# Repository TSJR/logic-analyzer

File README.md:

# TTL Logic Analyzer

Breadboard and PCB-based logic analyzer built from discrete 74xx TTL logic, SRAM, and multiplexed LED matrix displays.

## Overview
This project aims to build a fully discrete logic analyzer without using a microcontroller. The analyzer captures digital bus states into SRAM and displays captured samples on multiplexed LED matrices.

Project is currently in a state of active prototyping.

*This repository also contains a [closely related project](attiny-logic-analyzer) using an MCU-based design with 24 channels. 

## Features
- Fully TTL-based architecture
- SRAM-based sample capture
- Multiplexed LED matrix display
- External/internal clock modes
- Planned trigger and halt functionality
- Modular PCB-based design

## Current Status
Current prototype supports:
- 64ish x 8 sample memory subsystem
- LED matrix display driver
- Breadboard proof-of-concept testing

Known issues:
- Breadboard noise/signal integrity
- Clock edge instability
- Limited memory

## Architecture
Main subsystems:
- Capture memory subsystem
- Address/control logic
- Clock generation and edge conditioning
- Display subsystem

## Relevant Simulation Subcircuits
- `analyzer_7400.circ` — 74xx IC Implementation     
    - **mem_64x8**: Full memory subsystem test built from 74xx-style chips using four `ram_unit` subcircuits.
    - **ram_unit**: 16x8 RAM unit built from 74xx-style chips; used as the building block for `mem_64x8`.
    - **disp_16x16**: Limited-capacity display subsystem test; does not yet include the physical driver circuitry needed for hardware.
- `analyzer_ttl.circ` — Abstract Logic Implementation
    - **mem_64x8_async**: Asynchronous version of the 64x8 memory subsystem; same capacity as the final intended design.
    - **disp_16x32**: Full-capacity display subsystem test.

More detailed documentation:
- [Analyzer Architecture](docs/architecture.md)
- [Build Log](docs/build-log.md)
- [Simulation Subcircuits](simulations/sim-subcircuits.md)

## Repository Structure
```text
docs/                   Docs and architecture notes
images/                 Build photos and diagrams
pcb/                    KiCad PCB projects
simulations/            Logisim simulations
attiny-logic-analyzer/   Related MCU-based project
```

## Hardware
Main IC families/components:
- 74xx logic family chips
- ULN2803 and UDN2981

## Future Plans
- Expand memory depth
- Modular memory pcb
- Trigger logic
- Improved clock conditioning
- PCB-based final implementation

If the project expands beyond basic TTL hardware, plans may include
- USB interface
- OLED display
- Many more channels
- Higher sampling rate 

## License
MIT License

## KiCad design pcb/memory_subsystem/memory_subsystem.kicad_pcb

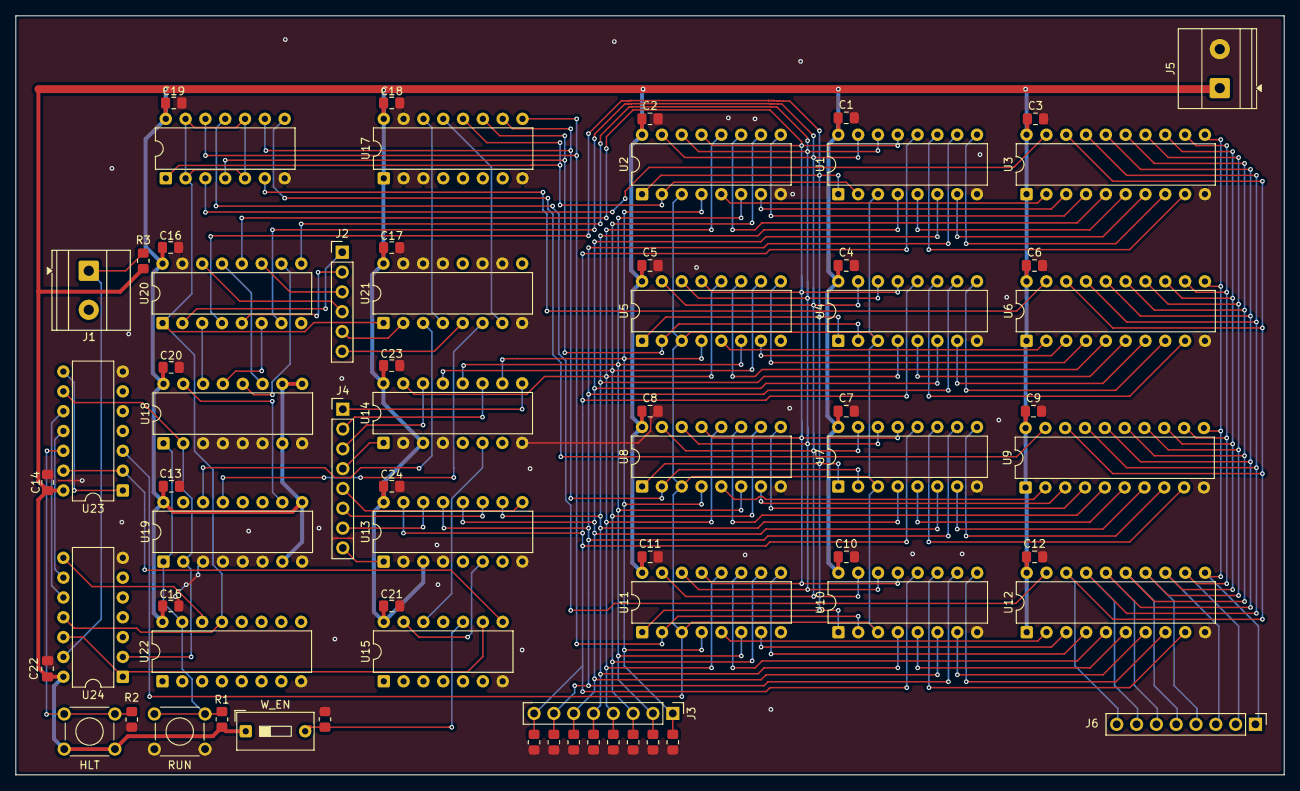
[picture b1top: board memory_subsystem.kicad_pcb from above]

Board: 2 copper layers, 162.6 x 97.3 mm, 69 parts (0 on the bottom side), 100 nets.

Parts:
C1, C2, C3, C4, C5, C6, C7, C8, C9, C10, C11, C12, C13, C14, C15, C16, C17, C18, C19, C20, C21, C22, C23, C24: C; C_0805_2012Metric_Pad1.18x1.45mm_HandSolder
HLT: HLT; SW_TH_Tactile_Omron_B3F-100x
J1: CLK; TerminalBlock_Phoenix_MKDS-1,5-2_1x02_P5.00mm_Horizontal
J2: Addr In; PinHeader_1x06_P2.54mm_Vertical
J3: Data In; PinHeader_1x08_P2.54mm_Vertical
J4: Word In; PinHeader_1x08_P2.54mm_Vertical
J5: Power; TerminalBlock_Phoenix_MKDS-1,5-2_1x02_P5.00mm_Horizontal
J6: Data Out; PinHeader_1x08_P2.54mm_Vertical
R1, R2, R3, R4, R5, R6, R7, R8, R9, R10, R11, R12: R; R_0805_2012Metric_Pad1.20x1.40mm_HandSolder
RUN: RUN; SW_TH_Tactile_Omron_B3F-100x
U1, U2, U4, U5, U7, U8, U10, U11: DIP-16_W7.62mm
U3, U6, U9, U12: 74LS245; DIP-20_W7.62mm
U13, U14: 74LS85; DIP-16_W7.62mm
U15: 74LS21; DIP-14_W7.62mm
U16, U23: 74LS32; DIP-14_W7.62mm
U17: 74LS139; DIP-16_W7.62mm
U18, U19: 74LS161; DIP-16_W7.62mm
U20, U21: 74LS157; DIP-16_W7.62mm
U22: 74LS279; DIP-16_W7.62mm
U24: 74LS14; DIP-14_W7.62mm
W_EN: W_EN; SW_DIP_SPSTx01_Slide_9.78x4.72mm_W7.62mm_P2.54mm

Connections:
+5V: C1.1, C2.1, C3.1, C4.1, C5.1, C6.1, C7.1, C8.1, C9.1, C10.1, C11.1, C12.1, C13.2, C14.2, C15.2, C16.2, C17.1, C18.2, C19.2, C20.2, C21.2, C22.2, C23.2, C24.2, HLT.1, J5.1, R1.1, R3.2, U1.16 (VCC), U2.16 (VCC), U3.1 (A->B), U3.20 (VCC), U4.16 (VCC), U5.16 (VCC), U6.1 (A->B), U6.20 (VCC), U7.16 (VCC), U8.16 (VCC), U9.1 (A->B), U9.20 (VCC), U10.16 (VCC), U11.16 (VCC), U12.1 (A->B), U12.20 (VCC), U13.3 (Ia=b), U13.16 (VCC), U14.3 (Ia=b), U14.16 (VCC), U15.14 (VCC), U16.14 (VCC), U17.1 (E), U17.16 (VCC), U18.7 (CEP), U18.9 (~PE), U18.10 (CET), U18.16 (VCC), U19.7 (CEP), U19.9 (~PE), U19.16 (VCC), U20.16 (VCC), U21.16 (VCC), U22.16 (VCC), U23.14 (VCC), U24.14 (VCC), W_EN.1
/Address Selector/Addr0: J2.1, U20.2 (I0a)
/Address Selector/Addr1: J2.2, U20.5 (I0b)
/Address Selector/Addr2: J2.3, U20.11 (I0c)
/Address Selector/Addr3: J2.4, U20.14 (I0d)
/Address Selector/Addr4: J2.5, U21.2 (I0a)
/Address Selector/Addr5: J2.6, U21.5 (I0b)
/Address Selector/CS0: U1.2 (CS), U2.2 (CS), U16.1, U17.12 (O0)
/Address Selector/CS1: U4.2 (CS), U5.2 (CS), U16.4, U17.11 (O1)
/Address Selector/CS2: U7.2 (CS), U8.2 (CS), U16.9, U17.10 (O2)
/Address Selector/CS3: U10.2 (CS), U11.2 (CS), U16.12, U17.9 (O3)
/Address Selector/OE0: U3.19 (CE), U16.3
/Address Selector/OE1: U6.19 (CE), U16.6
/Address Selector/OE2: U9.19 (CE), U16.8
/Address Selector/OE3: U12.19 (CE), U16.11
/Address Selector/RUN: R1.2, RUN.2, U18.1 (~MR), U19.1 (~MR), U22.15 (~S)
/Address Selector/R/W: U16.2, U16.5, U16.10, U16.13, U20.1 (S), U21.1 (S), U22.13 (Q), U24.11
/Address Selector/SAddr0: U1.1 (A0), U2.1 (A0), U4.1 (A0), U5.1 (A0), U7.1 (A0), U8.1 (A0), U10.1 (A0), U11.1 (A0), U20.4 (Za)
/Address Selector/SAddr1: U1.15 (A1), U2.15 (A1), U4.15 (A1), U5.15 (A1), U7.15 (A1), U8.15 (A1), U10.15 (A1), U11.15 (A1), U20.7 (Zb)
/Address Selector/SAddr2: U1.14 (A2), U2.14 (A2), U4.14 (A2), U5.14 (A2), U7.14 (A2), U8.14 (A2), U10.14 (A2), U11.14 (A2), U20.9 (Zc)
/Address Selector/SAddr3: U1.13 (A3), U2.13 (A3), U4.13 (A3), U5.13 (A3), U7.13 (A3), U8.13 (A3), U10.13 (A3), U11.13 (A3), U20.12 (Zd)
/Address Selector/SAddr4: U17.14 (A0), U21.4 (Za)
/Address Selector/SAddr5: U17.13 (A1), U21.7 (Zb)
/Address Selector/counter_CLK: U18.2 (CP), U19.2 (CP), U23.9, U24.2
/Control Logic/CLK: J1.1 (Pin_1_1), R3.1, U24.13
/Control Logic/RAM_WE: U1.3 (WE), U2.3 (WE), U4.3 (WE), U5.3 (WE), U7.3 (WE), U8.3 (WE), U10.3 (WE), U11.3 (WE), U23.3
/Control Logic/man_HLT: HLT.2, R2.2, U23.12
/Control Logic/word_CLK: U15.9, U24.1, U24.12
/Control Logic/word_HLT: U15.8, U23.2, U23.13
/Din0: J3.1, R5.1, U2.4 (D0), U5.4 (D0), U8.4 (D0), U11.4 (D0), U14.10 (A0)
/Din1: J3.2, R6.1, U2.6 (D1), U5.6 (D1), U8.6 (D1), U11.6 (D1), U14.12 (A1)
/Din2: J3.3, R7.1, U2.10 (D2), U5.10 (D2), U8.10 (D2), U11.10 (D2), U14.13 (A2)
/Din3: J3.4, R8.1, U2.12 (D3), U5.12 (D3), U8.12 (D3), U11.12 (D3), U14.15 (A3)
/Din4: J3.5, R9.1, U1.4 (D0), U4.4 (D0), U7.4 (D0), U10.4 (D0), U13.10 (A0)
/Din5: J3.6, R10.1, U1.6 (D1), U4.6 (D1), U7.6 (D1), U10.6 (D1), U13.12 (A1)
/Din6: J3.7, R11.1, U1.10 (D2), U4.10 (D2), U7.10 (D2), U10.10 (D2), U13.13 (A2)
/Din7: J3.8, R12.1, U1.12 (D3), U4.12 (D3), U7.12 (D3), U10.12 (D3), U13.15 (A3)
/Out0: J6.8, U3.18 (B0), U6.18 (B0), U9.18 (B0), U12.18 (B0)
/Out1: J6.7, U3.17 (B1), U6.17 (B1), U9.17 (B1), U12.17 (B1)
/Out2: J6.6, U3.16 (B2), U6.16 (B2), U9.16 (B2), U12.16 (B2)
/Out3: J6.5, U3.15 (B3), U6.15 (B3), U9.15 (B3), U12.15 (B3)
/Out4: J6.4, U3.14 (B4), U6.14 (B4), U9.14 (B4), U12.14 (B4)
/Out5: J6.3, U3.13 (B5), U6.13 (B5), U9.13 (B5), U12.13 (B5)
/Out6: J6.2, U3.12 (B6), U6.12 (B6), U9.12 (B6), U12.12 (B6)
/Out7: J6.1, U3.11 (B7), U6.11 (B7), U9.11 (B7), U12.11 (B7)
/Win0: J4.1, U14.9 (B0)
/Win1: J4.2, U14.11 (B1)
/Win2: J4.3, U14.14 (B2)
/Win3: J4.4, U14.1 (B3)
/Win4: J4.5, U13.9 (B0)
/Win5: J4.6, U13.11 (B1)
/Win6: J4.7, U13.14 (B2)
/Win7: J4.8, U13.1 (B3)
/Word Comparator/word_EN: R4.1, U15.10, W_EN.2
GND: C1.2, C2.2, C3.2, C4.2, C5.2, C6.2, C7.2, C8.2, C9.2, C10.2, C11.2, C12.2, C13.1, C14.1, C15.1, C16.1, C17.2, C18.1, C19.1, C20.1, C21.1, C22.1, C23.1, C24.1, J5.2, R2.1, R4.2, R5.2, R6.2, R7.2, R8.2, R9.2, R10.2, R11.2, R12.2, RUN.1, U1.8 (GND), U2.8 (GND), U3.10 (GND), U4.8 (GND), U5.8 (GND), U6.10 (GND), U7.8 (GND), U8.8 (GND), U9.10 (GND), U10.8 (GND), U11.8 (GND), U12.10 (GND), U13.2 (Ia<b), U13.4 (Ia>b), U13.8 (GND), U14.2 (Ia<b), U14.4 (Ia>b), U14.8 (GND), U15.7 (GND), U16.7 (GND), U17.2 (A0), U17.3 (A1), U17.8 (GND), U17.15 (E), U18.3 (D0), U18.4 (D1), U18.5 (D2), U18.6 (D3), U18.8 (GND), U19.3 (D0), U19.4 (D1), U19.5 (D2), U19.6 (D3), U19.8 (GND), U20.8 (GND), U20.15 (E), U21.8 (GND), U21.10 (I1c), U21.11 (I0c), U21.13 (I1d), U21.14 (I0d), U21.15 (E), U22.8 (GND), U23.7 (GND), U24.7 (GND)
unnamed: U1.5 (O0), U3.6 (A4)
unnamed: U1.7 (O1), U3.7 (A5)
unnamed: U1.9 (O2), U3.8 (A6)
unnamed: U1.11 (O3), U3.9 (A7)
unnamed: U2.5 (O0), U3.2 (A0)
unnamed: U2.7 (O1), U3.3 (A1)
unnamed: U2.9 (O2), U3.4 (A2)
unnamed: U2.11 (O3), U3.5 (A3)
unnamed: U4.5 (O0), U6.6 (A4)
unnamed: U4.7 (O1), U6.7 (A5)
unnamed: U4.9 (O2), U6.8 (A6)
unnamed: U4.11 (O3), U6.9 (A7)
unnamed: U5.5 (O0), U6.2 (A0)
unnamed: U5.7 (O1), U6.3 (A1)
unnamed: U5.9 (O2), U6.4 (A2)
unnamed: U5.11 (O3), U6.5 (A3)
unnamed: U7.5 (O0), U9.6 (A4)
unnamed: U7.7 (O1), U9.7 (A5)
unnamed: U7.9 (O2), U9.8 (A6)
unnamed: U7.11 (O3), U9.9 (A7)
unnamed: U8.5 (O0), U9.2 (A0)
unnamed: U8.7 (O1), U9.3 (A1)
unnamed: U8.9 (O2), U9.4 (A2)
unnamed: U8.11 (O3), U9.5 (A3)
unnamed: U10.5 (O0), U12.6 (A4)
unnamed: U10.7 (O1), U12.7 (A5)
unnamed: U10.9 (O2), U12.8 (A6)
unnamed: U10.11 (O3), U12.9 (A7)
unnamed: U11.5 (O0), U12.2 (A0)
unnamed: U11.7 (O1), U12.3 (A1)
unnamed: U11.9 (O2), U12.4 (A2)
unnamed: U11.11 (O3), U12.5 (A3)
unnamed: U13.6 (Oa=b), U15.13
unnamed: U14.6 (Oa=b), U15.12
unnamed: U18.14 (Q0), U20.3 (I1a)
unnamed: U18.13 (Q1), U20.6 (I1b)
unnamed: U18.12 (Q2), U20.10 (I1c)
unnamed: U18.11 (Q3), U20.13 (I1d)
unnamed: U18.15 (TC), U19.10 (CET)
unnamed: U19.14 (Q0), U21.3 (I1a)
unnamed: U19.13 (Q1), U21.6 (I1b)
unnamed: U22.14 (~R), U24.8
unnamed: U23.1, U23.8
unnamed: U23.10, U24.10
unnamed: U23.11, U24.9

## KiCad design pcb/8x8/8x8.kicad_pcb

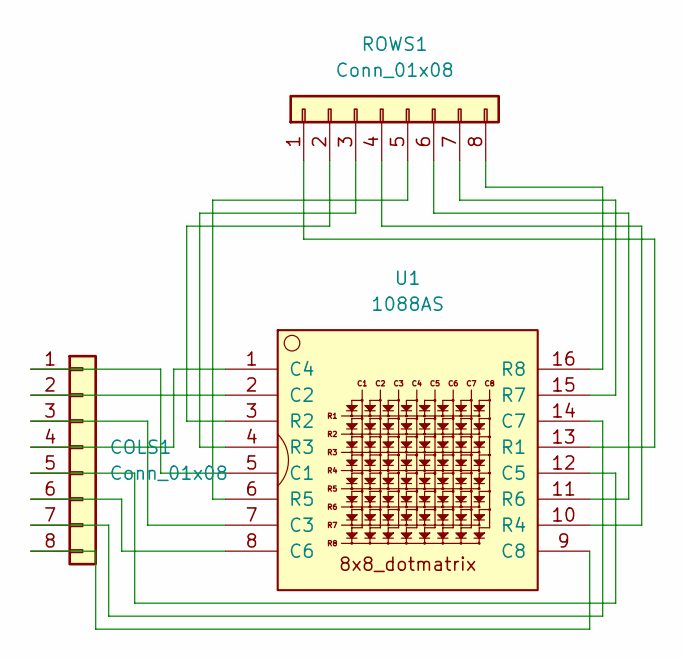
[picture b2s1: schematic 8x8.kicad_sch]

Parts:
COLS1: Conn_01x08; PinSocket_1x08_P2.54mm_Vertical
ROWS1: Conn_01x08; PinSocket_1x08_P2.54mm_Vertical
U1: 1088AS; LED_1088_Pin_Header

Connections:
unnamed: COLS1.1, U1.5 (C1)
unnamed: COLS1.2, U1.2 (C2)
unnamed: COLS1.3, U1.7 (C3)
unnamed: COLS1.4, U1.1 (C4)
unnamed: COLS1.5, U1.12 (C5)
unnamed: COLS1.6, U1.8 (C6)
unnamed: COLS1.7, U1.14 (C7)
unnamed: COLS1.8, U1.9 (C8)
unnamed: ROWS1.1, U1.13 (R1)
unnamed: ROWS1.2, U1.3 (R2)
unnamed: ROWS1.3, U1.4 (R3)
unnamed: ROWS1.4, U1.10 (R4)
unnamed: ROWS1.5, U1.6 (R5)
unnamed: ROWS1.6, U1.11 (R6)
unnamed: ROWS1.7, U1.15 (R7)
unnamed: ROWS1.8, U1.16 (R8)

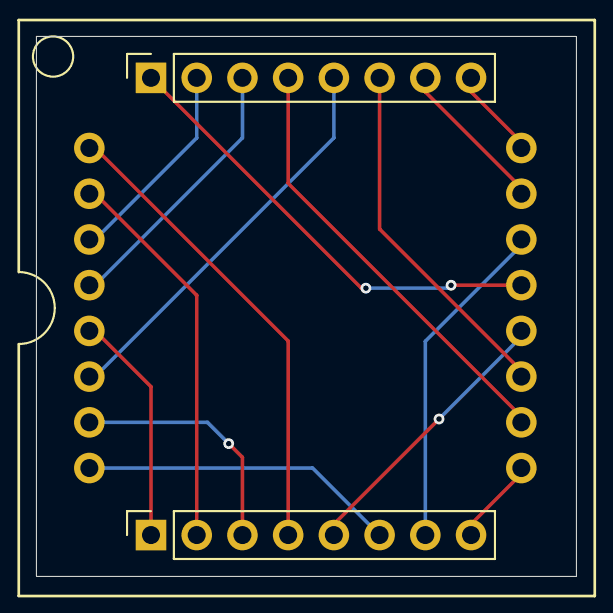
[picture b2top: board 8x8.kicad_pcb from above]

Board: 2 copper layers, 30.0 x 30.0 mm, 3 parts (0 on the bottom side), 16 nets.

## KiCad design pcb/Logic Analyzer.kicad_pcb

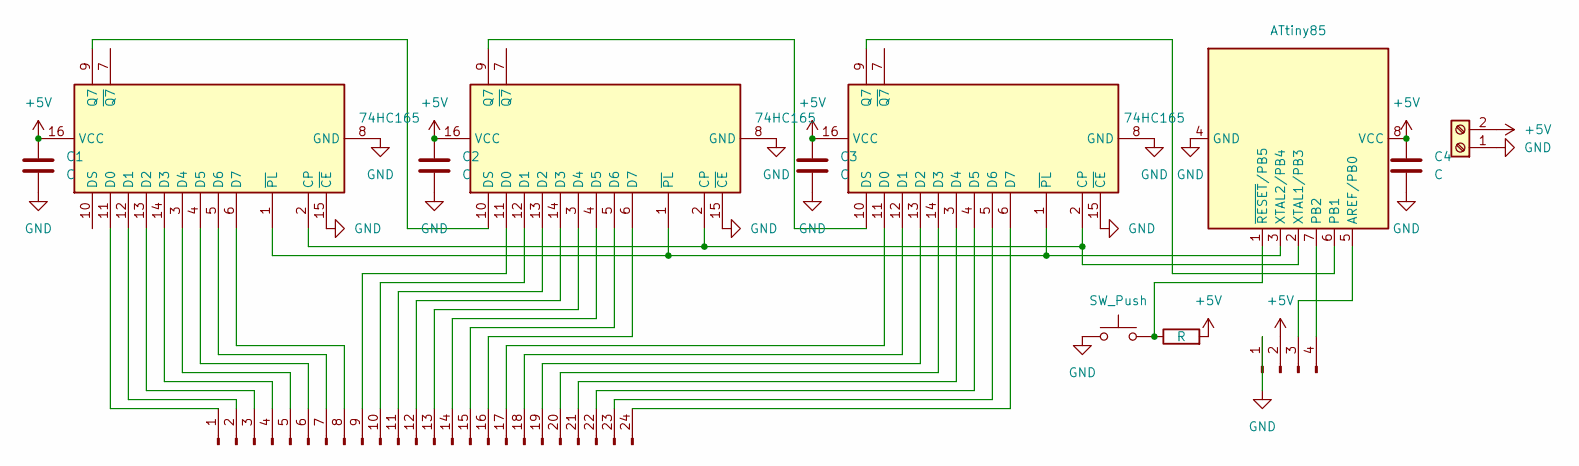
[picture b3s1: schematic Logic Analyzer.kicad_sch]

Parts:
C1, C2, C3, C4: C; C_Disc_D7.0mm_W2.5mm_P5.00mm
J1: Conn_01x24_Pin; PinHeader_1x24_P2.54mm_Vertical
J2: Conn_01x04_Pin; PinHeader_1x04_P2.54mm_Vertical
J3: Screw_Terminal_01x02; TerminalBlock_Phoenix_MKDS-1,5-2-5.08_1x02_P5.08mm_Horizont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
R1: R; R_Axial_DIN0207_L6.3mm_D2.5mm_P7.62mm_Horizontal
SW1: SW_Push; SW_PUSH_6mm
U1, U2, U3: 74HC165; DIP-16_W7.62mm
U4: ATtiny85; DIP-8_W7.62mm

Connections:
+5V: C1.1, C2.1, C3.1, C4.1, J2.2, J3.2, R1.2, U1.16 (VCC), U2.16 (VCC), U3.16 (VCC), U4.8 (VCC)
GND: C1.2, C2.2, C3.2, C4.2, J2.1, J3.1, SW1.1, U1.8 (GND), U1.15 (~CE), U2.8 (GND), U2.15 (~CE), U3.8 (GND), U3.15 (~CE), U4.4 (GND)
unnamed: J1.1, U1.11 (D0)
unnamed: J1.2, U1.12 (D1)
unnamed: J1.3, U1.13 (D2)
unnamed: J1.4, U1.14 (D3)
unnamed: J1.5, U1.3 (D4)
unnamed: J1.6, U1.4 (D5)
unnamed: J1.7, U1.5 (D6)
unnamed: J1.8, U1.6 (D7)
unnamed: J1.9, U2.11 (D0)
unnamed: J1.10, U2.12 (D1)
unnamed: J1.11, U2.13 (D2)
unnamed: J1.12, U2.14 (D3)
unnamed: J1.13, U2.3 (D4)
unnamed: J1.14, U2.4 (D5)
unnamed: J1.15, U2.5 (D6)
unnamed: J1.16, U2.6 (D7)
unnamed: J1.17, U3.11 (D0)
unnamed: J1.18, U3.12 (D1)
unnamed: J1.19, U3.13 (D2)
unnamed: J1.20, U3.14 (D3)
unnamed: J1.21, U3.3 (D4)
unnamed: J1.22, U3.4 (D5)
unnamed: J1.23, U3.5 (D6)
unnamed: J1.24, U3.6 (D7)
unnamed: J2.3, U4.5 (AREF/PB0)
unnamed: J2.4, U4.7 (PB2)
unnamed: U1.2 (CP), U2.2 (CP), U3.2 (CP), U4.2 (XTAL1/PB3)
unnamed: U1.9 (Q7), U2.10 (DS)
unnamed: U1.1 (~PL), U2.1 (~PL), U3.1 (~PL), U4.3 (XTAL2/PB4)
unnamed: U2.9 (Q7), U3.10 (DS)
unnamed: U3.9 (Q7), U4.6 (PB1)
unnamed: R1.1, SW1.2, U4.1 (~RESET/PB5)

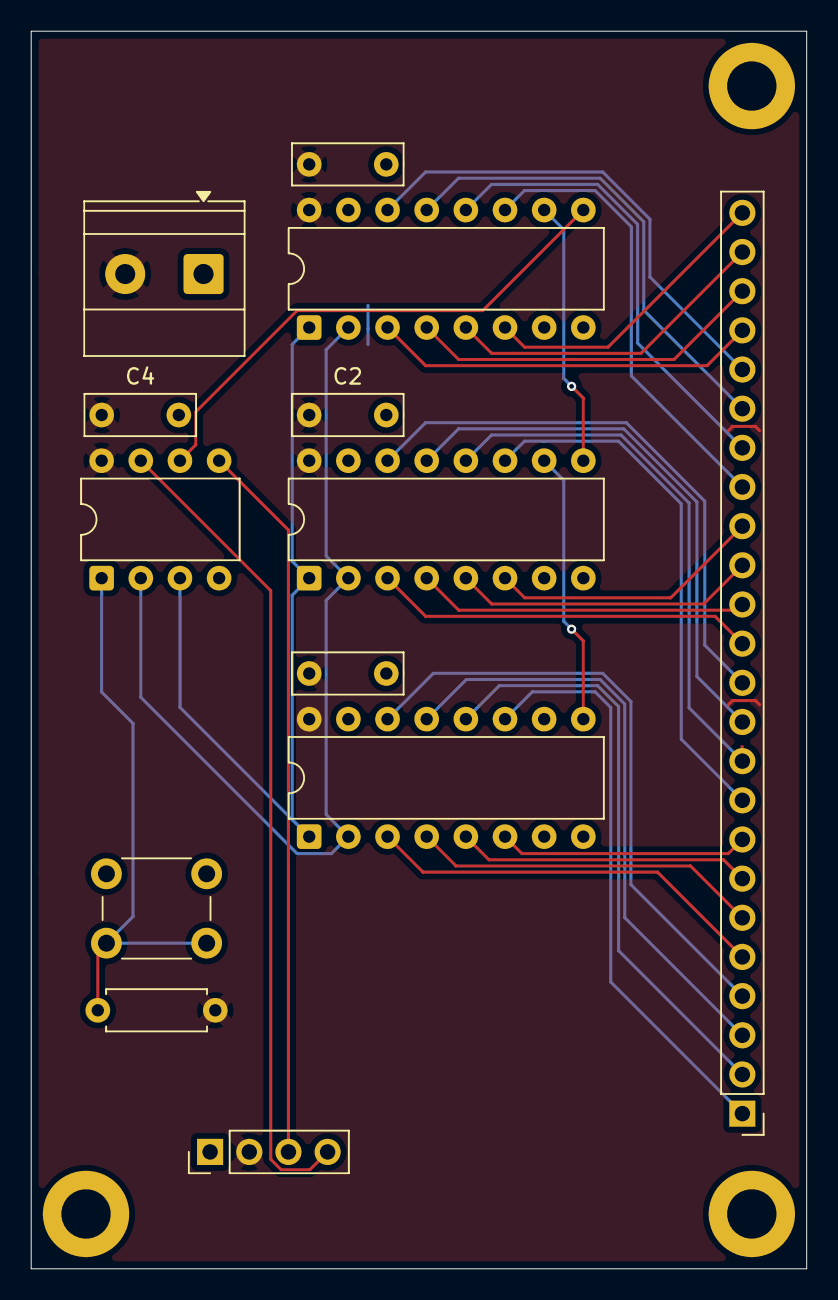
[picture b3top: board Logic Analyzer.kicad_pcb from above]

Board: 2 copper layers, 50.3 x 80.3 mm, 13 parts (0 on the bottom side), 34 nets.

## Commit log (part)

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2026-04-24 Init
2026-04-24 test
2026-05-02 TTL files added Filenames updated
2026-05-02 Renamed files
2026-05-12 File architecture edited, 8x8 dotmat pcb added
2026-05-25 Improving docs Added architecture.md to give current plan for memory side layout
2026-05-26 chore: add gitignore
2026-05-26 Chore: added .gitignore
2026-05-26 Chore: added todo
2026-05-26 Improved layout
2026-05-26 Updated todo
2026-05-27 Build log 5/22
2026-05-27 Chore: cleaned .gitignore files
2026-05-27 Build log 5/23
2026-05-27 Chore: updated todo
2026-05-27 Added README.md
2026-05-27 Updated build log
2026-05-27 Match new breadboard design
2026-05-27 Adjusted to match current design
2026-05-28 Added sim subcircuit description
2026-05-28 64x8 mem subsystem finished
2026-06-06 Secondary project repository added
2026-06-06 Added ATtiny project info
2026-06-06 Memory unit debugging
2026-06-08 HLT Word operation fixed to fit current design
2026-06-09 Updated build log 6/8
2026-06-09 Updated progress pic
2026-06-09 Updated build log 6/8 pt 2
2026-06-14 Started memory subsystem schematic
2026-06-22 Finished first draft of memory subsystem
